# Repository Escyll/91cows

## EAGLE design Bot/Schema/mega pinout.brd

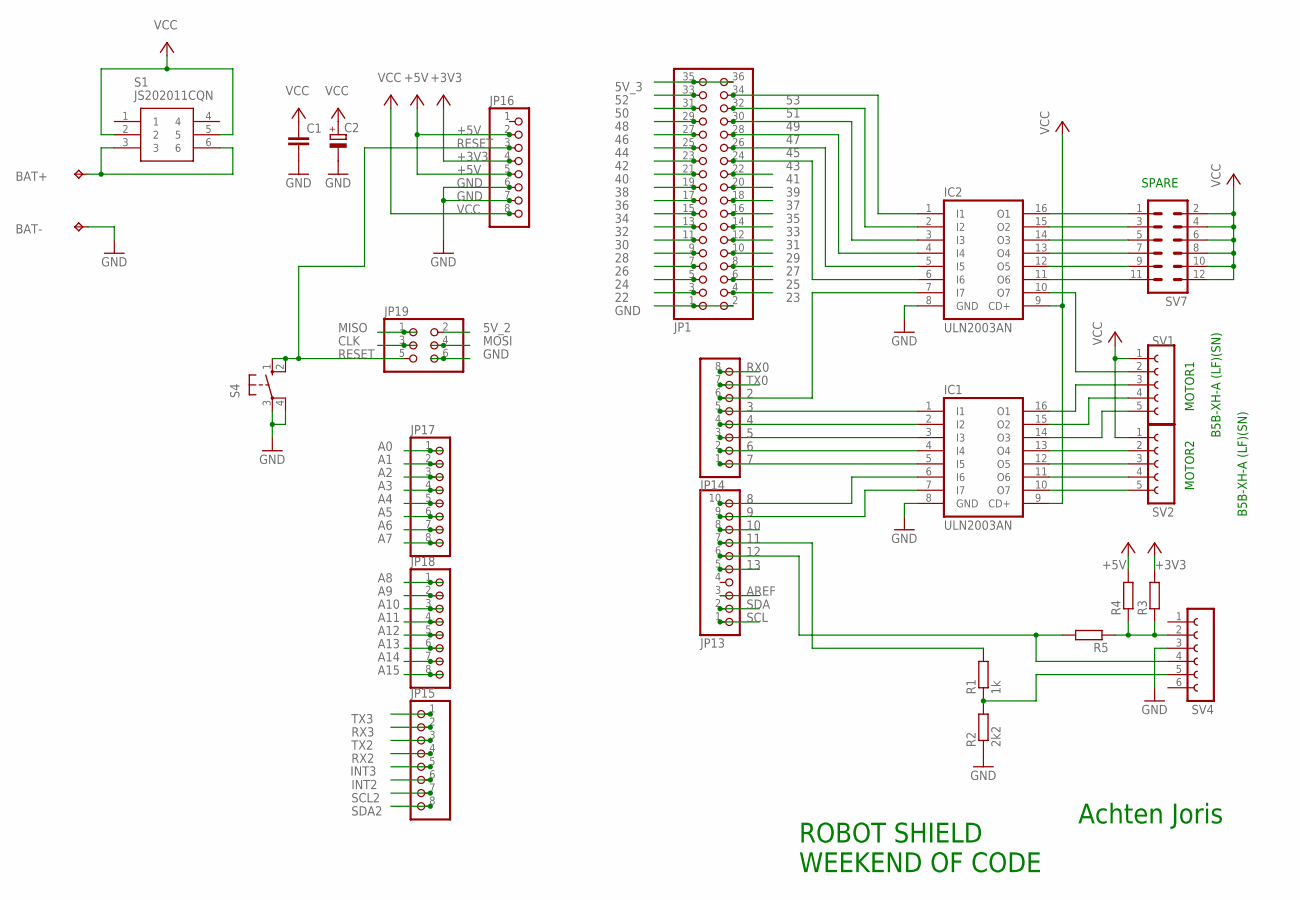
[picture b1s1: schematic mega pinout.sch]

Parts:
BAT+: TPPAD1-13; P1-13
BAT-: TPPAD1-13; P1-13
C1: C-EUC1206; C1206
C2: CPOL-EUE5-8.5; E5-8,5
IC1, IC2: ULN2003AN; DIL16
JP1: PINHD-2X18; 2X18
JP13: PINHD-1X10; 1X10
JP14, JP15, JP16, JP17, JP18: PINHD-1X8; 1X08
JP19: PINHD-2X3; 2X03
R1: 1k; R0603
R2: 2k2; R0603
R3, R4, R5: R-EU_R0603; R0603
S1: JS202011CQN
S4: 10-XX; B3F-10XX
SV1, SV2: FE05-1
SV4: FE06-1; FE06
SV7: MA06-2

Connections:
2: IC2.7 (I7), JP14.6
3: IC1.1 (I1), JP14.5
4: IC1.2 (I2), JP14.4
5: IC1.3 (I3), JP14.3
5V_2: JP19.2
5V_3: JP1.35, JP1.36
6: IC1.4 (I4), JP14.2
7: IC1.5 (I5), JP14.1
8: IC1.6 (I6), JP13.10
9: IC1.7 (I7), JP13.9
10: JP13.8
11: JP13.7, R1.2
12: JP13.6, R5.2, SV4.4
13: JP13.5
22: JP1.3
23: JP1.4
24: JP1.5
25: JP1.6
26: JP1.7
27: JP1.8
28: JP1.9
29: JP1.10
30: JP1.11
31: JP1.12
32: JP1.13
33: JP1.14
34: JP1.15
35: JP1.16
36: JP1.17
37: JP1.18
38: JP1.19
39: JP1.20
40: JP1.21
41: JP1.22
42: JP1.23
43: IC2.6 (I6), JP1.24
44: JP1.25
45: IC2.5 (I5), JP1.26
46: JP1.27
47: IC2.4 (I4), JP1.28
48: JP1.29
49: IC2.3 (I3), JP1.30
50: JP1.31
51: IC2.2 (I2), JP1.32
52: JP1.33
53: IC2.1 (I1), JP1.34
+3V3: JP16.4, R3.2
+5V: JP16.2, JP16.5, R4.2
A0: JP17.1
A1: JP17.2
A2: JP17.3
A3: JP17.4
A4: JP17.5
A5: JP17.6
A6: JP17.7
A7: JP17.8
A8: JP18.1
A9: JP18.2
A10: JP18.3
A11: JP18.4
A12: JP18.5
A13: JP18.6
A14: JP18.7
A15: JP18.8
AREF: JP13.3
CLK: JP19.3
GND: BAT-.TP, C1.2, C2.-, IC1.8 (GND), IC2.8 (GND), JP1.1, JP1.2, JP16.6, JP16.7, JP19.6, R2.1, S4.3, S4.4 (P1), SV4.3
INT2: JP15.6
INT3: JP15.5
MISO: JP19.1
MOSI: JP19.4
unnamed: BAT+.TP, S1.3, S1.6
unnamed: R1.1, R2.2, SV4.5
unnamed: IC1.10 (O7), SV2.5
unnamed: IC1.11 (O6), SV2.4
unnamed: IC1.12 (O5), SV2.3
unnamed: IC1.13 (O4), SV2.2
unnamed: IC1.14 (O3), SV1.5
unnamed: IC1.15 (O2), SV1.4
unnamed: IC1.16 (O1), SV1.3
unnamed: IC2.10 (O7), SV1.2
unnamed: IC2.16 (O1), SV7.1
unnamed: IC2.15 (O2), SV7.3
unnamed: IC2.14 (O3), SV7.5
unnamed: IC2.13 (O4), SV7.7
unnamed: IC2.12 (O5), SV7.9
unnamed: IC2.11 (O6), SV7.11
unnamed: R3.1, R4.1, R5.1, SV4.2
RESET: JP16.3, JP19.5, S4.1 (S), S4.2 (S1)
RX0: JP14.8
RX2: JP15.4
RX3: JP15.2
SCL: JP13.1
SCL2: JP15.7
SDA: JP13.2
SDA2: JP15.8
TX0: JP14.7
TX2: JP15.3
TX3: JP15.1
VCC: C1.1, C2.+, IC1.9 (CD+), IC2.9 (CD+), JP16.8, S1.2, S1.5, SV1.1, SV2.1, SV7.2, SV7.4, SV7.6, SV7.8, SV7.10, SV7.12

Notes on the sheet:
MOTOR1
MOTOR2
ROBOT SHIELD WEEKEND OF CODE
Achten Joris
SPARE
B5B-XH-A (LF)(SN)

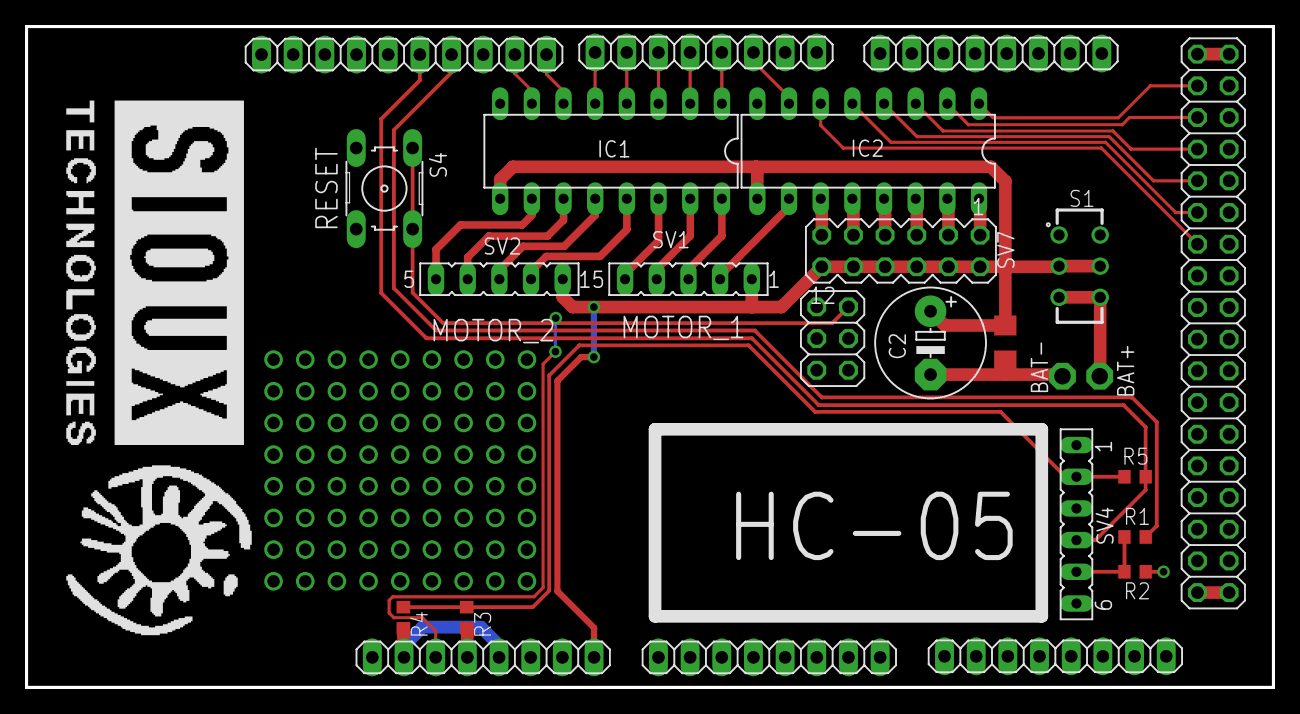
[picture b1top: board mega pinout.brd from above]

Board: 2 copper layers, 100.0 x 53.0 mm, 25 parts (0 on the bottom side), 39 nets.

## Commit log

2019-06-12 Added gitignore
2019-07-10 Basic C# sample application to communicate through TCP connection with C++ game engine
2019-07-12 Add .gitignore
2019-07-12 Add initial GameService, CommunicationLib and Fake apps
2019-08-07 Added initial list and prototype code for the Bot
2019-08-11 bot: Add proof of concept for bluetooth controlled bot.
2019-08-18 Add models for the prototype parts
2019-08-19 initial commit for bot tracker service
2019-08-20 Added mazeJson generator
2019-08-21 Update bot program to work with two motors and up/down/turn left/turn right commands.
2019-08-21 Add gitignore for Bot folder
2019-08-21 Update bot stuff list with bluetooth module name
2019-08-25 Camera calibration
2019-08-25 Update models to reduce width of the bot to around 10cm.
2019-08-25 Update/Add reference links.
2019-08-25 Added artwork for visualisation and base folder for unity
2019-08-25 Empty 2D unity project, setup for git version control
2019-08-25 Render of tilemaps, seperated ground and wall but static render
2019-08-25 Bot tracker complete (without transmitting coordinates)
2019-08-26 JSON GameDataModel
2019-08-26 unit test json parser
2019-08-26 Now running at full 1080p resolution
2019-08-26 Ground tiles and wall tiles with orientation
2019-08-27 Scalable UI section, optimize groundtile rendering and randomize base ground tile orientation
2019-08-27 Plugin deps
2019-08-27 car, color can be set in code
2019-08-29 Render json ticks from folder @ 30fps. Render bot position, rotation to be checked for correctness
2019-08-30 Added sockets for all parties/clients
2019-08-31 Add MazeLib and MazeGenerator
2019-09-01 bot coloring improved by separating sprite into static and colored part
2019-09-01 Add parse command logic to bot logic.
2019-09-01 Items tilesheet, coin anim from tilesheet sprites
2019-09-01 Added multiple item animations
2019-09-02 direction and debug rays
2019-09-04 Json.Net for unity
2019-09-08 Update the list of stuff for the bot
2019-09-08 Add schema for the bot
2019-09-08 Add model where the wheelholder is replaced with printed ball.
2019-09-17 cleanup, server + connect ui
2019-09-17 scrollable scoreboard, static items that need filling in
2019-09-18 Added start of game loop, collision detection and flipped maze y-axis.
2019-09-24 added TCP communication layer
2019-09-24 tweak communicator
2019-09-26 Added bot tracker service simulator
2019-09-26 updated help text
2019-09-26 Created README
    Added usage description for the simulator
2019-09-26 Removed tempory unity project data
2019-09-27 New stuff
2019-09-29 Add project setup for BotController
2019-09-29 Added playing field extent selection utility
2019-09-29 Add first working manual control:
    Interface to bot remained the same.
2019-09-29 Add bot add-on for the battery pack and AR marker
2019-09-29 Update gitignore to support multiple version of Arduino IDE
2019-09-29 Add parsing of bot locations
2019-09-29 Rename handleActionTiles to handleActionItems
2019-09-30 Add random placement of actionItems
2019-10-02 Newest stuff
2019-10-02 Integration settings 1
2019-10-02 Update the stuff we need for the bot
2019-10-02 Fixed stuff
2019-10-05 Updated sim file for jesper
2019-10-05 Moved data recording to its own class and linting
2019-10-06 add first version of the wall collition
2019-10-08 Refactor the wall collision code
2019-10-08 add corner wall collision logic
2019-10-08 create game loop and add handle action items
2019-10-08 add has action item collision
2019-10-08 add action item and game logc
2019-10-09 Fixed build issues
2019-10-09 BotController: Add example.env and add explanation for use of manual control.
2019-10-09 Bot/Models: Update to latest models and add print settings.
2019-10-09 Bot: Update stuff we need per bot.
2019-10-09 Bot/Model: Update ARMarker holder to accomodate for a bigger connector.
2019-10-09 Bot/Models: Add space for batterypack add-on screw driver.
2019-10-09 Working collision detection
2019-10-16 updated simulation with 3 robots in real world
2019-10-16 More stuff
2019-10-21 Improve stuff
2019-10-21 Bot/testBT: Update \n to \r and disable the serial printing.
2019-10-21 fix bug that test tube was not working
2019-10-23 BotController: Update README to include different connection applciations.
2019-10-23 BotController: Add remote control via local server using HTTP GET.
2019-10-23 BotController: Update pnpm-lock with updated dependecies and new module.
2019-10-23 BotController: Remove unnecessary TODO.
2019-10-23 BotController: Update README to include first connection setup based on address.
2019-10-23 final prep day changes
2019-10-24 Maze game visualisation version 1.0 release
2019-10-24 Fixes
2019-10-25 Update README.md
    update node version
2019-10-25 BotController: Fix README inconsitencies and add basic build commands.
2019-10-31 Bot: Add Eagle schemas for the Arduino Shield and move schema related files to folder.
2019-10-31 Bot: Move model files to Model Folder.
2019-10-31 PuBotController: Add python control logic for BotControl.
2019-12-12 Fix bug in item collision box
2022-06-22 Bump Newtonsoft.Json in /Visualization/SupportPlugins/GameDataModel
    Bumps [Newtonsoft.Json](https://github.com/JamesNK/Newtonsoft.Json) from 12.0.2 to 13.0.1.
    - [Release notes](https://github.com/JamesNK/Newtonsoft.Json/releases)
    - [Commits](https://github.com/JamesNK/Newtonsoft.Json/compare/12.0.2...13.0.1)
    ---
    updated-dependencies:
    - dependency-name: Newtonsoft.Json
2022-12-08 Bump Newtonsoft.Json in /Visualization/SupportPlugins/GameDataModel
    Bumps [Newtonsoft.Json](https://github.com/JamesNK/Newtonsoft.Json) from 12.0.2 to 13.0.2.
    - [Release notes](https://github.com/JamesNK/Newtonsoft.Json/releases)
    - [Commits](https://github.com/JamesNK/Newtonsoft.Json/compare/12.0.2...13.0.2)
    ---
    updated-dependencies:
    - dependency-name: Newtonsoft.Json
